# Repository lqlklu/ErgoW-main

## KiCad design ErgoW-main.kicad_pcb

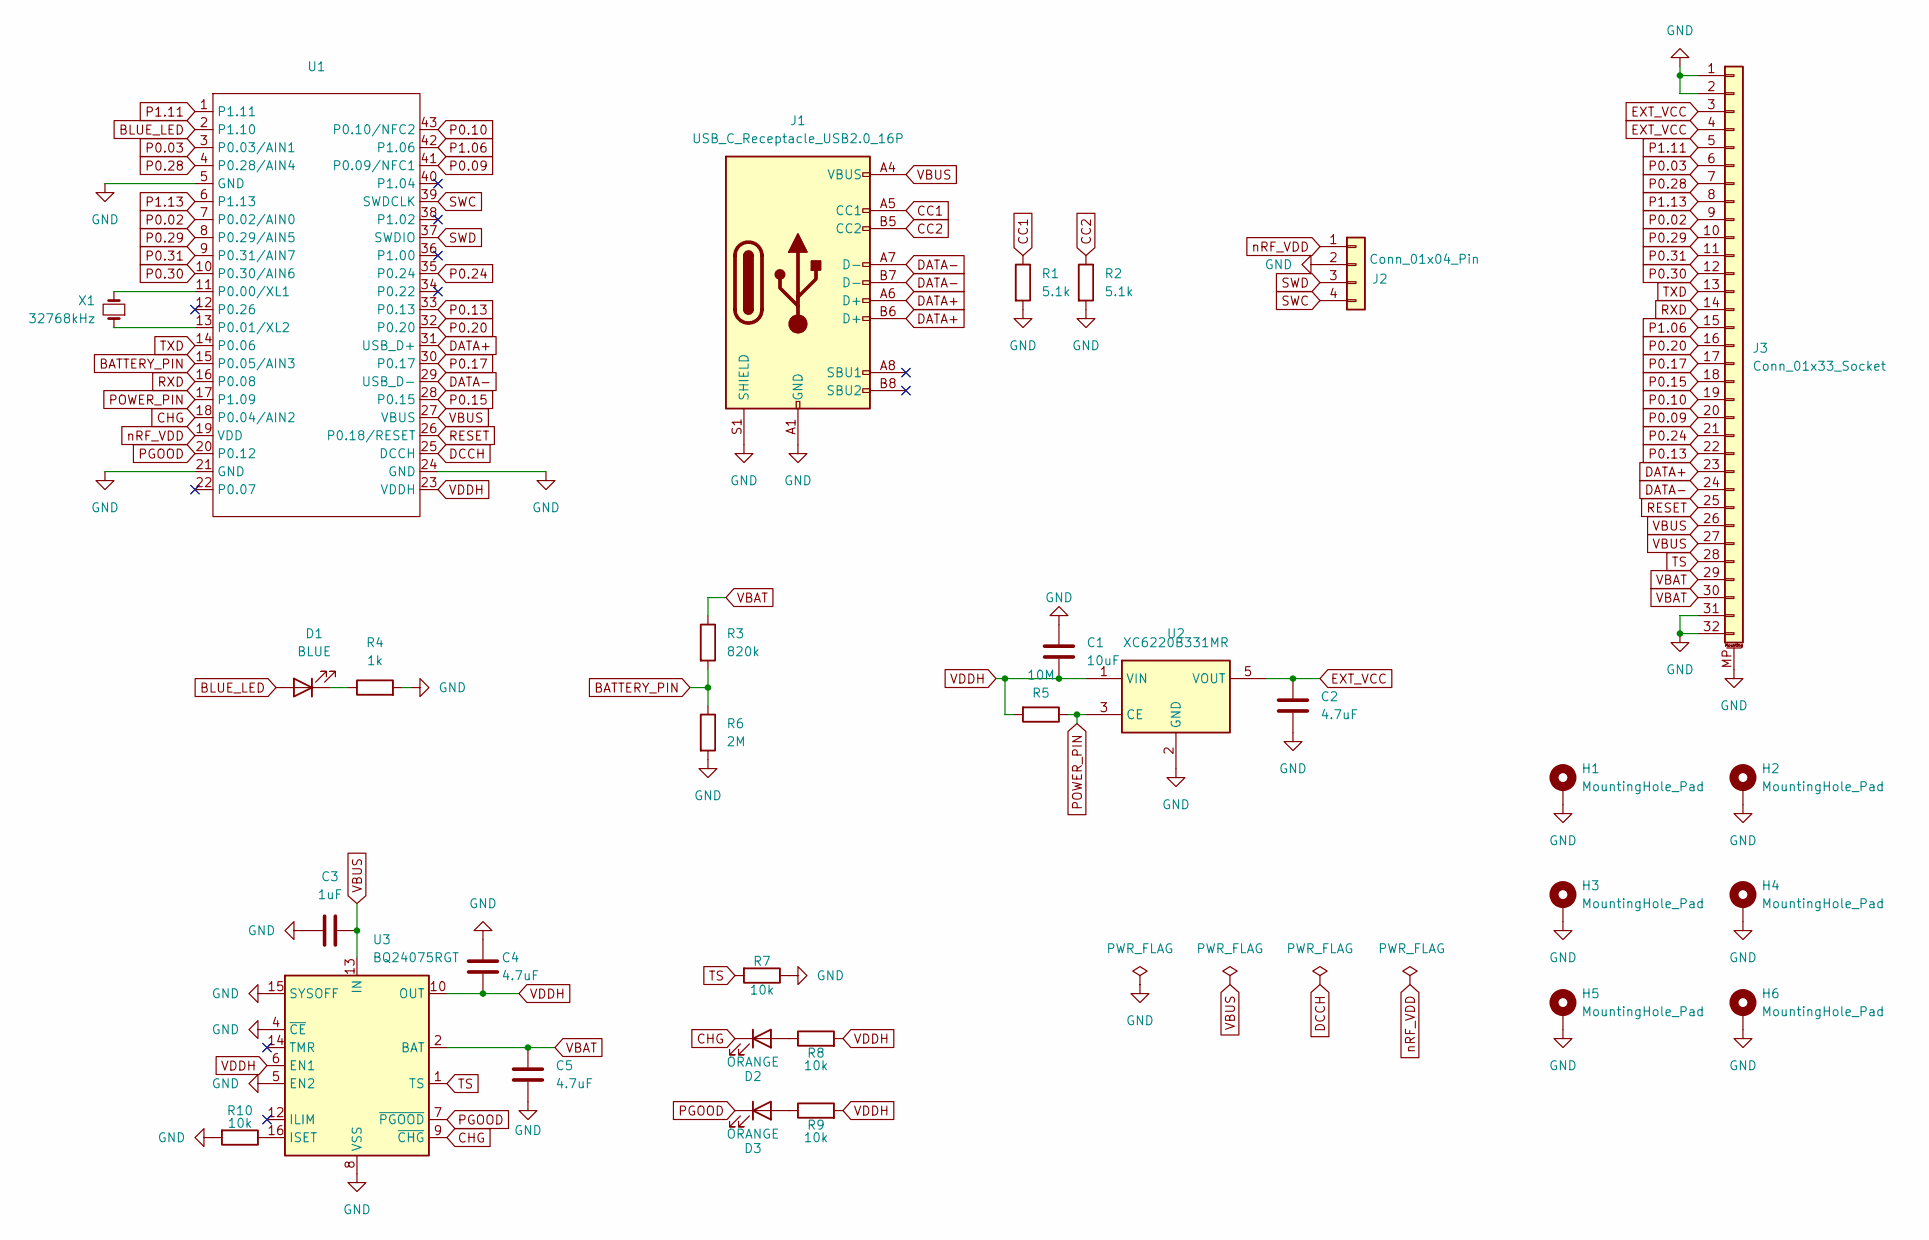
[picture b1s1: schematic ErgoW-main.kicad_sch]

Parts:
C1: 10uF; C_0603_1608Metric
C2, C4, C5: 4.7uF; C_0603_1608Metric
C3: 1uF; C_0603_1608Metric
D1: BLUE; LED_0603_1608Metric
D2, D3: ORANGE; LED_0603_1608Metric
H1, H2, H3, H4, H5, H6: MountingHole_Pad; MountingHole_2.2mm_M2_ISO7380_Pad_TopBottom
J1: USB_C_Receptacle_USB2.0_16P; USB_C_Receptacle_HCTL_HC-TYPE-C-16P-01A
J2: Conn_01x04_Pin; PinHeader_1x04_P1.00mm_Vertical
J3: Conn_01x33_Socket; Hirose_FH12-32S-0.5SH_1x32-1MP_P0.50mm_Horizontal
R1, R2: 5.1k; R_0402_1005Metric
R3: 820k; R_0402_1005Metric
R4: 1k; R_0402_1005Metric
R5: 10M; R_0402_1005Metric
R6: 2M; R_0402_1005Metric
R7, R8, R9, R10: 10k; R_0402_1005Metric
U1: E73-2G4M08S1C-52840
U2: XC6220B331MR; SOT-23-5
U3: BQ24075RGT; VQFN-16-1EP_3x3mm_P0.5mm_EP1.6x1.6mm
X1: 32768kHz; Crystal_SMD_3215-2Pin_3.2x1.5mm

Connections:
BATTERY_PIN: R3.2, R6.1, U1.15 (P0.05/AIN3)
BLUE_LED: D1.2 (A), U1.2 (P1.10)
CC1: J1.A5 (CC1), R1.1
CC2: J1.B5 (CC2), R2.1
CHG: D2.1 (K), U1.18 (P0.04/AIN2), U3.9 (~CHG)
DATA+: J1.A6 (D+), J1.B6 (D+), J3.23, U1.31 (USB_D+)
DATA-: J1.A7 (D-), J1.B7 (D-), J3.24, U1.29 (USB_D-)
DCCH: U1.25 (DCCH)
EXT_VCC: C2.2, J3.3, J3.4, U2.5 (VOUT)
GND: C1.1, C2.1, C3.1, C4.1, C5.2, H1.1, H2.1, H3.1, H4.1, H5.1, H6.1, J1.A1 (GND), J1.A12 (GND), J1.B1 (GND), J1.B12 (GND), J1.S1 (SHIELD), J2.2, J3.1, J3.2, J3.31, J3.32, J3.MP (MountPin), R1.2, R2.2, R4.2, R6.2, R7.1, R10.2, U1.5 (GND), U1.21 (GND), U1.24 (GND), U2.2 (GND), U3.4 (~CE), U3.5 (EN2), U3.8 (VSS), U3.15 (SYSOFF), U3.17 (VSS)
unnamed: D1.1 (K), R4.1
unnamed: D2.2 (A), R8.1
unnamed: D3.2 (A), R9.1
unnamed: U1.11 (P0.00/XL1), X1.2
unnamed: U1.13 (P0.01/XL2), X1.1
unnamed: R10.1, U3.16 (ISET)
P0.02: J3.9, U1.7 (P0.02/AIN0)
P0.03: J3.6, U1.3 (P0.03/AIN1)
P0.09: J3.20, U1.41 (P0.09/NFC1)
P0.10: J3.19, U1.43 (P0.10/NFC2)
P0.13: J3.22, U1.33 (P0.13)
P0.15: J3.18, U1.28 (P0.15)
P0.17: J3.17, U1.30 (P0.17)
P0.20: J3.16, U1.32 (P0.20)
P0.24: J3.21, U1.35 (P0.24)
P0.28: J3.7, U1.4 (P0.28/AIN4)
P0.29: J3.10, U1.8 (P0.29/AIN5)
P0.30: J3.12, U1.10 (P0.30/AIN6)
P0.31: J3.11, U1.9 (P0.31/AIN7)
P1.06: J3.15, U1.42 (P1.06)
P1.11: J3.5, U1.1 (P1.11)
P1.13: J3.8, U1.6 (P1.13)
PGOOD: D3.1 (K), U1.20 (P0.12), U3.7 (~PGOOD)
POWER_PIN: R5.1, U1.17 (P1.09), U2.3 (CE)
RESET: J3.25, U1.26 (P0.18/RESET)
RXD: J3.14, U1.16 (P0.08)
SWC: J2.4, U1.39 (SWDCLK)
SWD: J2.3, U1.37 (SWDIO)
TS: J3.28, R7.2, U3.1 (TS)
TXD: J3.13, U1.14 (P0.06)
VBAT: C5.1, J3.29, J3.30, R3.1, U3.2 (BAT), U3.3 (BAT)
VBUS: C3.2, J1.A4 (VBUS), J1.A9 (VBUS), J1.B4 (VBUS), J1.B9 (VBUS), J3.26, J3.27, U1.27 (VBUS), U3.13 (IN)
VDDH: C1.2, C4.2, R5.2, R8.2, R9.2, U1.23 (VDDH), U2.1 (VIN), U3.6 (EN1), U3.10 (OUT), U3.11 (OUT)
nRF_VDD: J2.1, U1.19 (VDD)

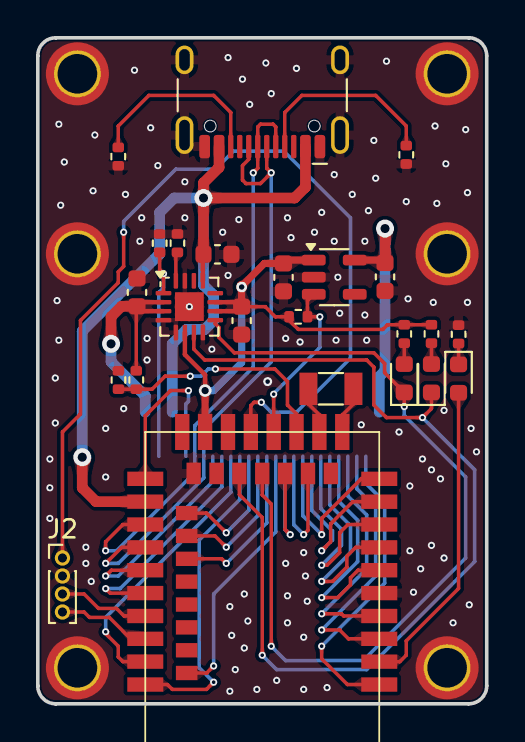
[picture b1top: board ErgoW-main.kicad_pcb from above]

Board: 2 copper layers, 24.9 x 37.0 mm, 31 parts (1 on the bottom side), 43 nets.

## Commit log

2025-07-06 init: 2025.07.06 version
2025-07-13 refactor: debug 3pin->4pin
